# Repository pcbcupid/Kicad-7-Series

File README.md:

# Kicad-7-Series
This repo is a collection of project files to a series of KiCad 7 tutorial, Which will take you through the journey of learning KiCad from scratch to making your first Printed Circuit Board.
 
 ## Video Resource
  
 * Kicad Development Series As Playlist : https://www.youtube.com/playlist?list=PLn6004q9oeqGl91KifK6xHGuqvXGb374G
 * Kicad Development Series As Articles : https://pcbcupid.com/posts/category/tutorial/
 * Kicad Development Series As Compiled Version : https://www.youtube.com/watch?v=KgmsvopC9Qk
 * Project Prototype Video : https://www.youtube.com/shorts/tJBAuqj2w3I

## Series Content
* Introduction to Kicad
* Learning UI basic tools and Navigation
* Building Schematics
* Understanding Schematics tools
* Performing Electrical Rule Check
* Assigning Footprints
* Understanding PCB Stackup / Netclasses
* Understanding PCB Editor tools
* Placement of components / PCB Layout 
* Routing The PCB
* Performing Design Rule Check
* Creating Custom Symbols and Footprint
* PCB Optimization for Production
 
If you have any question or doubts regarding any of the project file, You can drop your questions here : https://pcbcupid.com/questions/

## Project Info

The project is based on a digital version of Diya, which is reactive to light and wind just like real Diya!

Diya - is an oil lamp made from clay or mud with a cotton wick dipped in Oil or ghee. These lamps are commonly used in the Indian subcontinent and they hold sacred prominence in Hindu, Sikh, Buddhist and Jain prayers as well as religious rituals, ceremonies and festivals including Diwali.

You can download the code and 3d mode for the project form here : https://github.com/Neutrino-1/SideQuest/tree/main/Reactive%20Diya

## Final Design 

### Kicad 3d Render Export

### Final Manufactured PCB

Fabrication Info : https://www.youtube.com/playlist?list=PLn6004q9oeqFoRfbEq5fEx3mE1cEnQz48

## More Project  

#### Checkout Our Youtube Channel : https://www.youtube.com/@pcbcupid

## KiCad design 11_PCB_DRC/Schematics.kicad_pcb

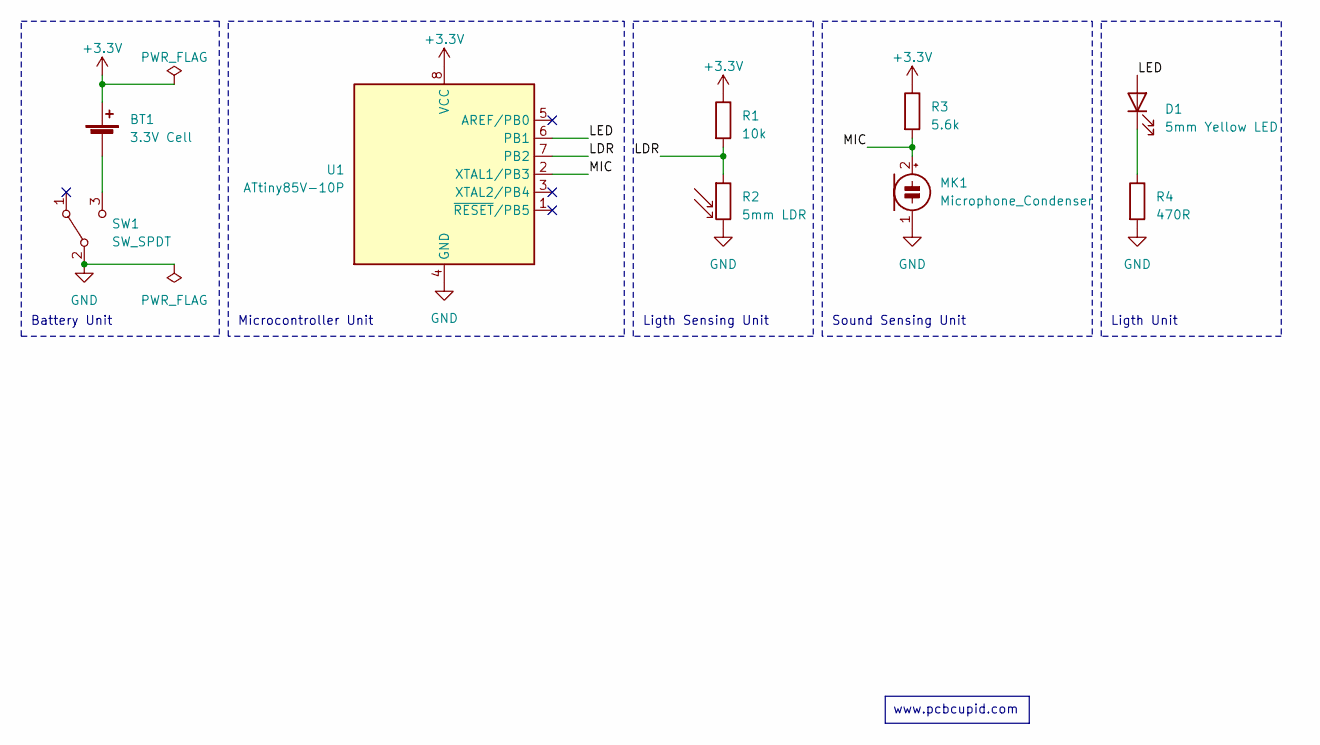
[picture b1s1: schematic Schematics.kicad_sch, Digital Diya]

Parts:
BT1: 3.3V Cell; BatteryHolder_ComfortableElectronic_CH273-2450_1x2450
D1: 5mm Yellow LED; LED_D5.0mm
MK1: Microphone_Condenser; PinHeader_1x02_P2.54mm_Vertical
R1: 10k; R_Axial_DIN0207_L6.3mm_D2.5mm_P15.24mm_Horizontal
R2: 5mm LDR; R_LDR_5.1x4.3mm_P3.4mm_Vertical
R3: 5.6k; R_Axial_DIN0207_L6.3mm_D2.5mm_P15.24mm_Horizontal
R4: 470R; R_Axial_DIN0207_L6.3mm_D2.5mm_P15.24mm_Horizontal
SW1: SW_SPDT; SW_CuK_OS102011MA1QN1_SPDT_Angled
U1: ATtiny85V-10P; DIP-8_W7.62mm

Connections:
+3.3V: BT1.1 (+), R1.1, R3.1, U1.8 (VCC)
/LDR: R1.2, R2.1, U1.7 (PB2)
/LED: D1.2 (A), U1.6 (PB1)
/MIC: MK1.2 (+), R3.2, U1.2 (XTAL1/PB3)
GND: MK1.1 (-), R2.2, R4.2, SW1.2 (B), U1.4 (GND)
unnamed: BT1.2 (-), SW1.3 (C)
unnamed: D1.1 (K), R4.1

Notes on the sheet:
www.pcbcupid.com
Ligth Unit
Microcontroller Unit
Ligth Sensing Unit
Sound Sensing Unit
Battery Unit

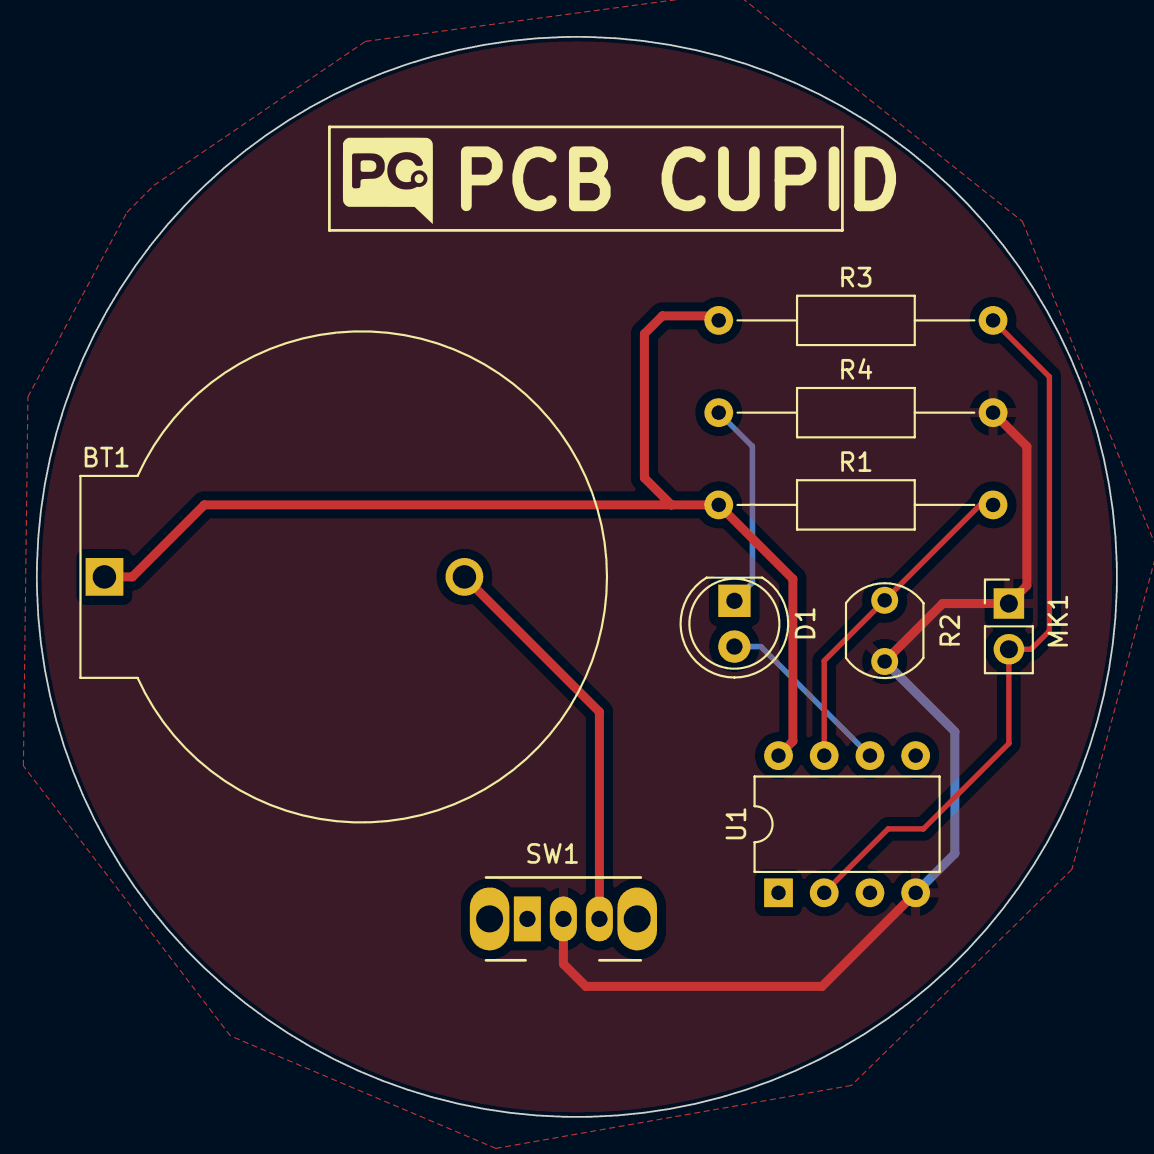
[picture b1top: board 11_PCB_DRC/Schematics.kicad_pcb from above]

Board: 2 copper layers, 60.0 x 60.0 mm, 9 parts (0 on the bottom side), 7 nets.

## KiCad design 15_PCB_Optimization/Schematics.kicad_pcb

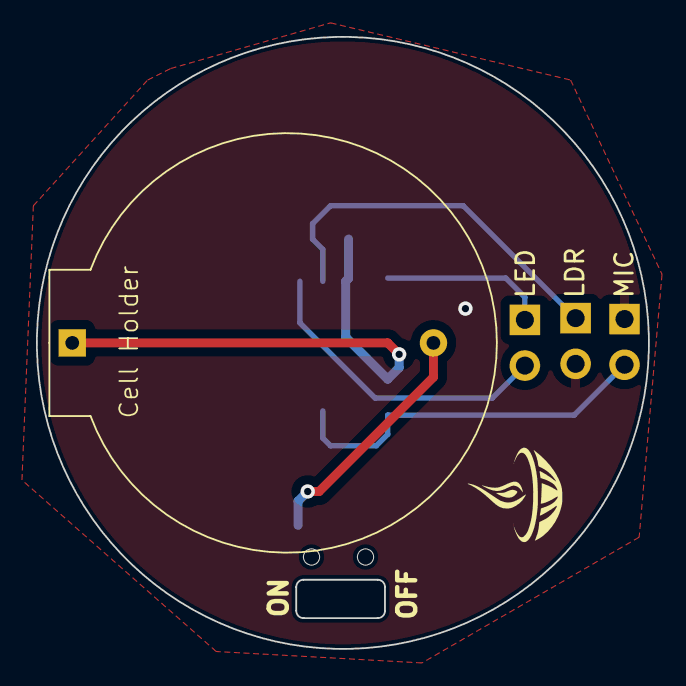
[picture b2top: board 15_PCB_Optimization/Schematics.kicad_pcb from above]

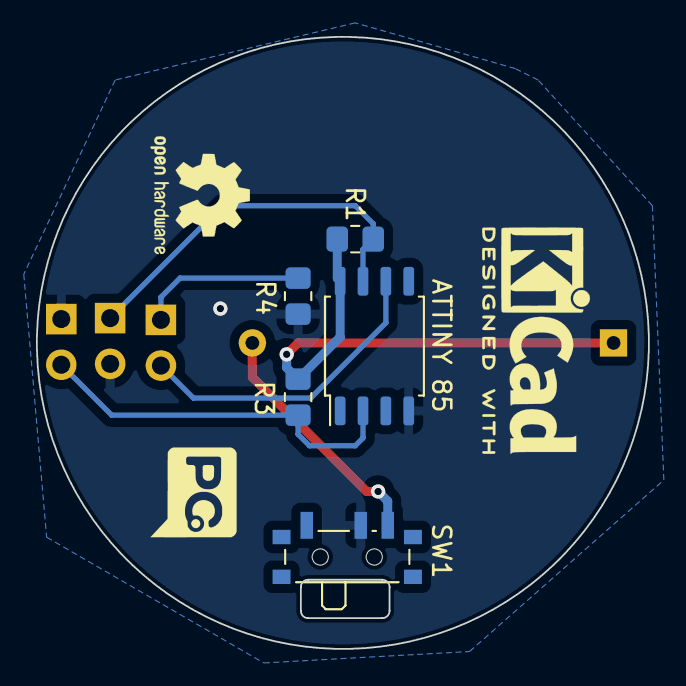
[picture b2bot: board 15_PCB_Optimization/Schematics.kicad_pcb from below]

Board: 2 copper layers, 34.0 x 34.0 mm, 9 parts (5 on the bottom side), 7 nets.

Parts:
ATTINY 85: ATtiny85V-10P; SOIC-8_5.275x5.275mm_P1.27mm
Cell Holder: 3.3V Cell; CellHolder_CR2032
LDR: 5mm LDR; PinHeader_1x02_P2.54mm_Vertical
LED: 5mm Yellow LED; PinHeader_1x02_P2.54mm_Vertical
MIC: Microphone_Condenser; PinHeader_1x02_P2.54mm_Vertical
R1: 10k; R_0805_2012Metric_Pad1.20x1.40mm_HandSolder
R3: 5.6k; R_0805_2012Metric_Pad1.20x1.40mm_HandSolder
R4: 470R; R_0805_2012Metric_Pad1.20x1.40mm_HandSolder
SW1: SW_SPDT; SW_SPDT_PCM12

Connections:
+3.3V: ATTINY 85.8 (VCC), Cell Holder.1 (+), R1.1, R3.1
/LDR: ATTINY 85.7 (PB2), LDR.1, R1.2
/LED: ATTINY 85.6 (PB1), LED.2 (A)
/MIC: ATTINY 85.2 (XTAL1/PB3), MIC.2 (+), R3.2
GND: ATTINY 85.4 (GND), LDR.2, MIC.1 (-), R4.2, SW1.2 (B)
unnamed: Cell Holder.2 (-), SW1.3 (C)
unnamed: LED.1 (K), R4.1

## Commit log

2023-02-24 Introduction video file commit
2023-02-24 Kicad User Interface Project file
2023-02-26 Creating schematic using Kicad
2023-02-27 added reference file
2023-02-27 Prettify Schematics
2023-03-02 Performing ERC
2023-03-05 Assign footprints to the symbols
2023-03-09 PCB stack up setup in PCB Layout Editor
2023-03-13 Kicad PCB Constraints and Net classes
2023-03-17 Placing the footprints
2023-03-21 routing
2023-03-27 DRC check + Custom Graphics
2023-04-01 Gerber Generation using KiCad
2023-04-05 Creating Custom Symbol
2023-04-09 Creating Custom footprint
2023-05-18 Backlink to CADLAB.io has been added.
2023-06-15 Demo Files added
